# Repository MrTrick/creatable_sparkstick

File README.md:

# creatable_sparkstick
OSHW designs for the Spark Stick ATTiny85 development board.

## Software
See https://github.com/nakatomi/creatable_srl

## License 
https://creativecommons.org/licenses/by-sa/3.0/

## Limitations
The Creatable and Spark Stick names and logos (or derivatives
thereof) may not be used as part of the name of a product,
company or domain name without express written permission.

## Disclaimer
Note: Schematics, source files, software, and datasheets are provided rovided "as is", without warranty of any kind, express or implied, including but not limited to the warranties of merchantability, fitness for a particular purpose and noninfringement. in no event shall the authors or copyright holders be liable for any claim, damages or other liability, whether in an action of contract, tort or otherwise, arising from, out of or in connection with the product or the use or other dealings in these products.

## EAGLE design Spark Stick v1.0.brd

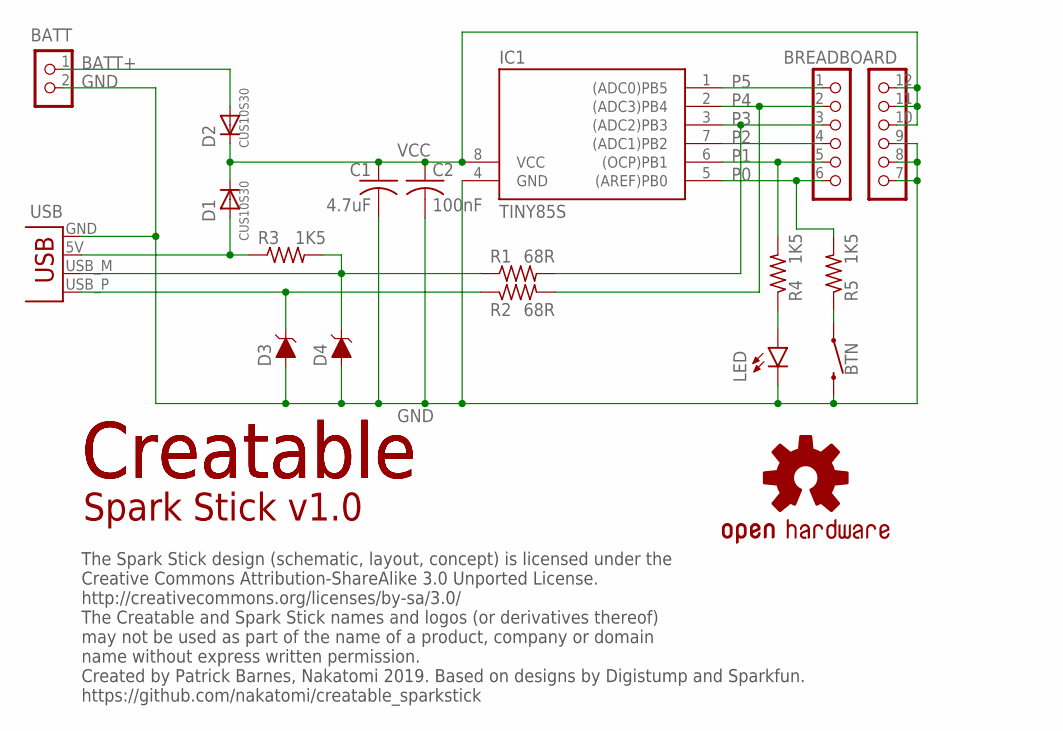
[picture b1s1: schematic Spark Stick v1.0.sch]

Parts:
BATT: CON_HEADER_1X02ROUND; CON_HEADER_M1X2_ROUND
BREADBOARD: CON_HEADER_2X06; CON_HEADER_M2X6_BREADBOARD
BTN: MOMENTARY-SWITCH-SPST-PTS810; PTS810SJG250SMTRLFS; LCSC_ID C221897
C1: 4.7uF; C0805K; LCSC_ID C107365
C2: 100nF; C0805K; LCSC_ID C1760
D1, D2: CUS10S30; SOD-323F; LCSC_ID C146335
D3, D4: DIODE-ZENER-SOD-323F; SOD-323F; LCSC_ID C353525
IC1: TINY85S; SOIC8; MPN ATTINY85-20SU; LCSC_ID C89852
LED: RED LED; LED-0603; LCSC_ID C125094
LOGO1: OSHW-LOGOM; OSHW-LOGO-M
LOGO_2A: LOGO_CREATABLECREAT; LOGO_CREATABLE_CREAT
LOGO_2B: LOGO_CREATABLEABLE; LOGO_CREATABLE_ABLE
R1, R2: 68R; R0603; LCSC_ID C192544
R3, R4, R5: 1K5; R0603; LCSC_ID C118361
USB: MICRO USB; SPARKFUN-CONNECTORS_USB-A-PCB

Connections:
BATT+: BATT.1, D2.A
BTN: BTN.1, BTN.2 (1), R5.1
D+: D3.C, R2.1, USB.USB_P (D+)
D-: D4.C, R1.1, R3.2, USB.USB_M (D-)
GND: BATT.2, BREADBOARD.7, BREADBOARD.8, BREADBOARD.9, BTN.3 (2), BTN.4 (2), C1.2, C2.2, D3.A, D4.A, IC1.4 (GND), LED.C, USB.GND
LED: LED.A, R4.1
P0: BREADBOARD.6, IC1.5 ((AREF)PB0), R5.2
P1: BREADBOARD.5, IC1.6 ((OCP)PB1), R4.2
P2: BREADBOARD.4, IC1.7 ((ADC1)PB2)
P3: BREADBOARD.3, IC1.3 ((ADC2)PB3), R1.2
P4: BREADBOARD.2, IC1.2 ((ADC3)PB4), R2.2
P5: BREADBOARD.1, IC1.1 ((ADC0)PB5)
VBUS: D1.A, R3.1, USB.5V (VBUS)
VCC: BREADBOARD.10, BREADBOARD.11, BREADBOARD.12, C1.1, C2.1, D1.C, D2.C, IC1.8 (VCC)

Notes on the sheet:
The Spark Stick design (schematic, layout, concept) is licensed under the Creative Commons Attribution-ShareAlike 3.0 Unported License. http://creativecommons.org/licenses/by-sa/3.0/ The Creatable and Spark Stick names and logos (or derivatives thereof) may not be used as part of the name of a prod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
Spark Stick v1.0

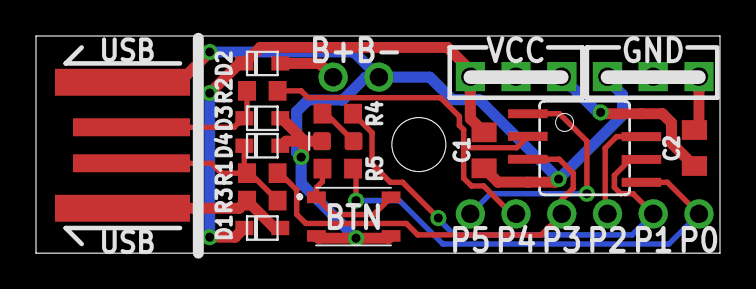
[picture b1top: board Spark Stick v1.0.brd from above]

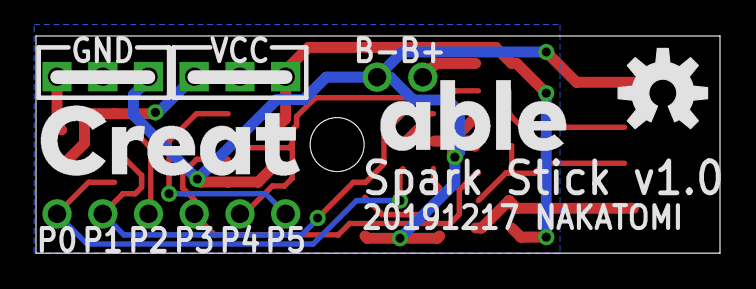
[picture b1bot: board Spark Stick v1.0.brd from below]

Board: 2 copper layers, 38.0 x 12.1 mm, 20 parts (3 on the bottom side), 14 nets.

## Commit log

2019-12-17 Added baseline files
2019-12-17 Added/fixed images

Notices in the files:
parts and their libraries:
SparkFun-Aesthetics: Licensing: Creative Commons ShareAlike 4.0 International - https://creativecommons.org/licenses/by-sa/4.0
